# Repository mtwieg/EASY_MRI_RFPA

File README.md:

# EASY_MRI_RFPA
Click the "Wiki" tab above to view the tutorials and other info!

DISCLAIMER:
None of the designs in this repo have been tested or certified to any safety standards (IEC 60601-1, UL-94, etc). 
Intended for non-clinical, research use only.
Circuits may involve hazardous voltages, currents, and temperatures.
For non-expert users, I highly recommend never touching the circuitry while power is being applied. Circuitry may be probed, but probes should not be moved or tampered with while power is applied.

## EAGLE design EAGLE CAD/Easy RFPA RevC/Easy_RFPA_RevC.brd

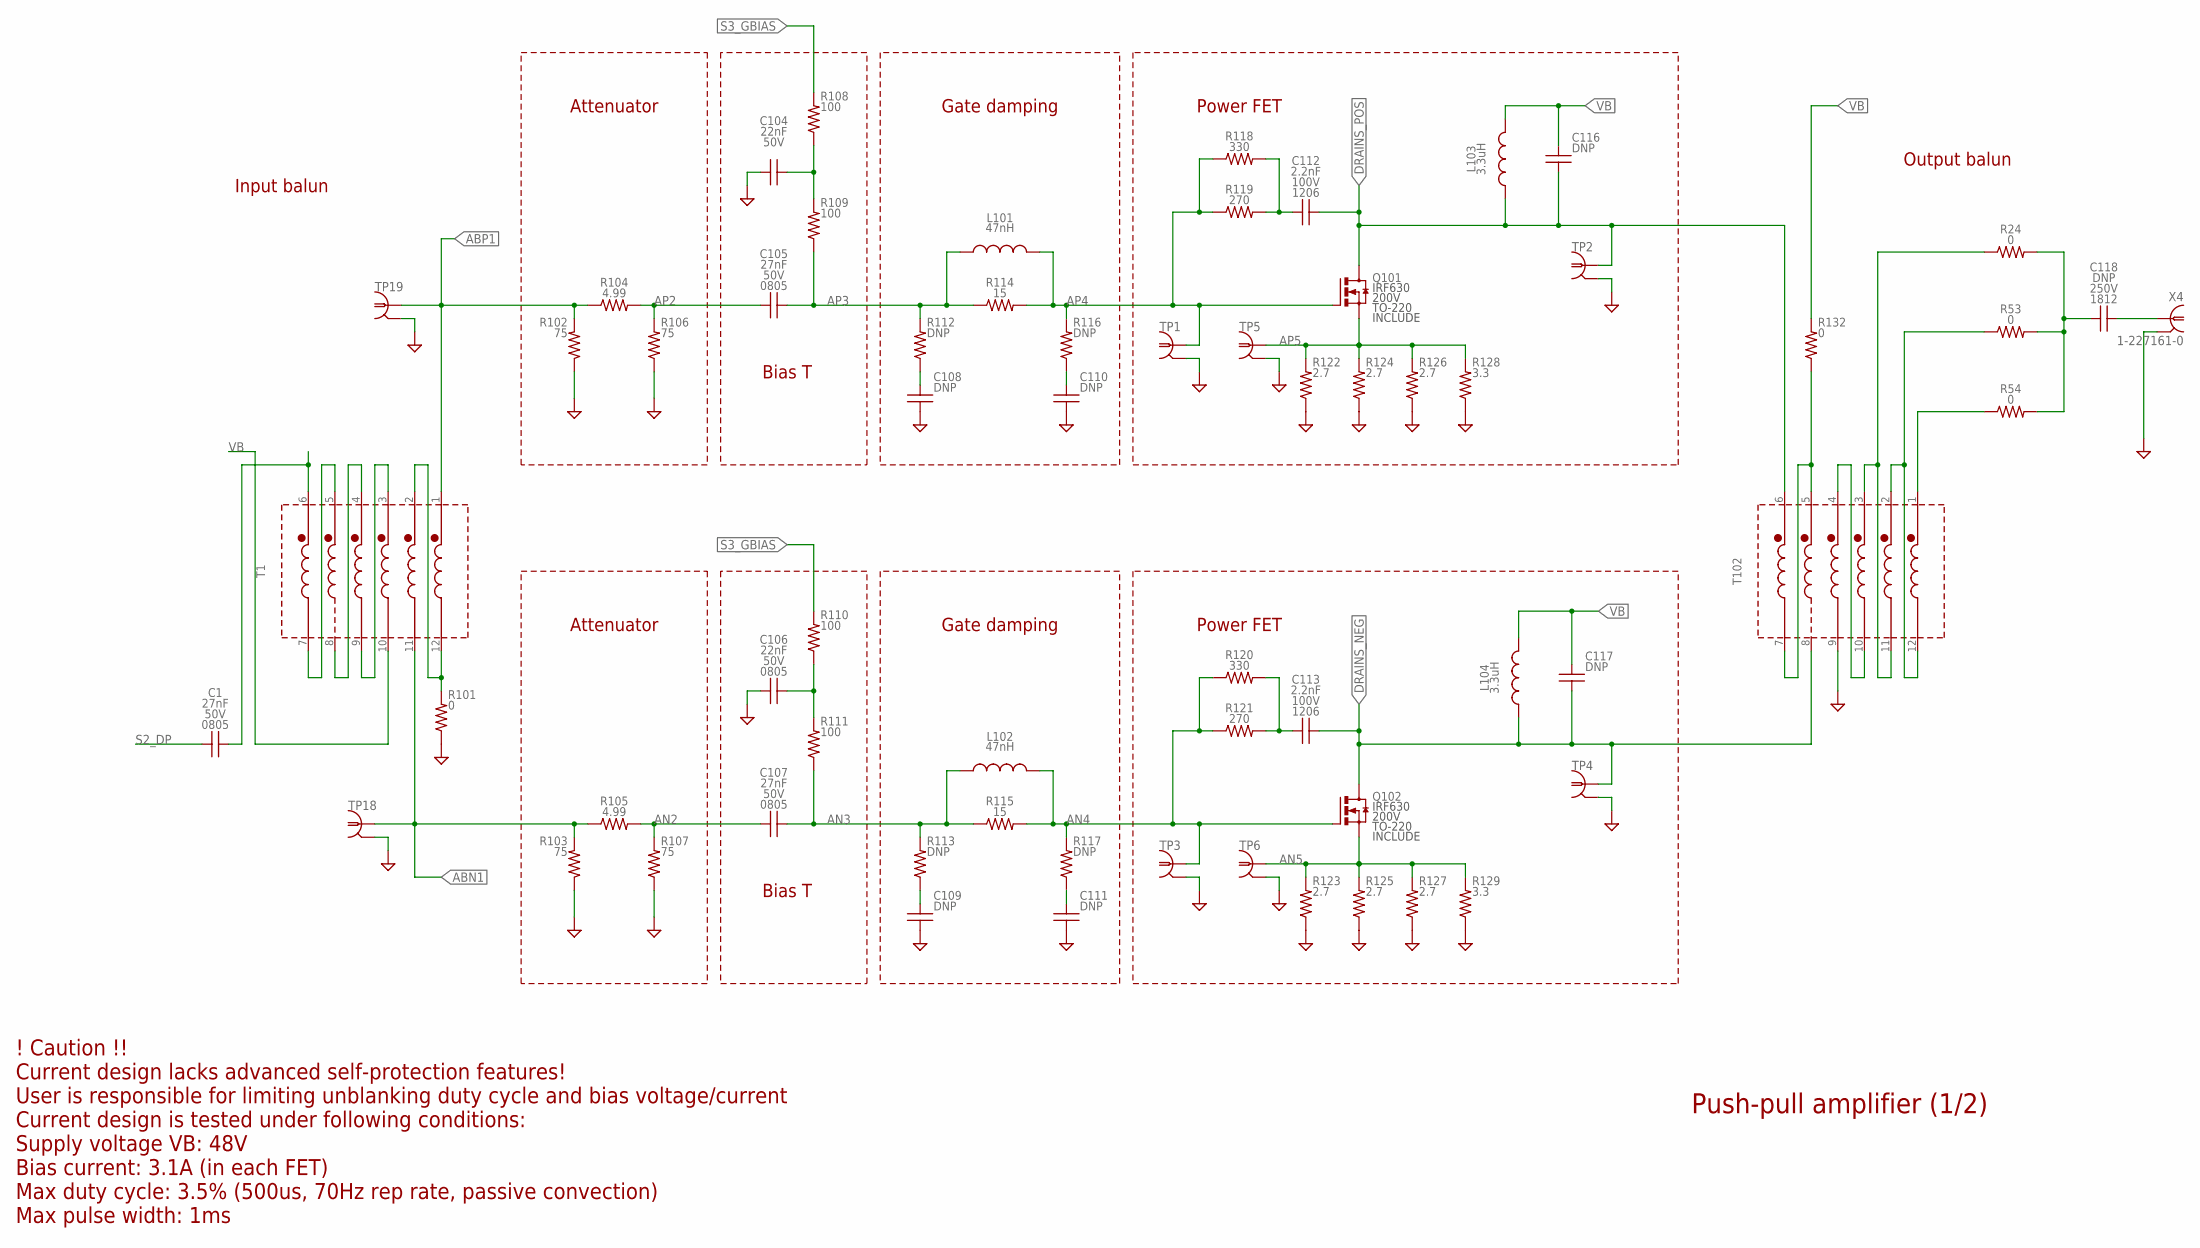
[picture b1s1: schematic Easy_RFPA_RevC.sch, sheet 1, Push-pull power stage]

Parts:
C1, C105, C107: 27nF; 0805_IPC-7351B; VOLTAGE 50V
C104, C106: 22nF; 0805_IPC-7351B; VOLTAGE 50V
C108, C109, C110, C111: DNP; 0805_IPC-7351B; VOLTAGE 50V
C112, C113: 2.2nF; C1206; VOLTAGE 100V
C116, C117: DNP; C1812; VOLTAGE 100V
C118: DNP; C1812; VOLTAGE 250V
L101, L102: 47nH; L1008
L103, L104: 3.3uH; DR127
Q101: IRF520N; TO220BV
Q102: IRF630; TO220BV
R24, R53, R54: 0; 1206_IPC-7351B
R101, R132: 0; 0805_IPC-7351B
R102, R103, R106, R107: 75; 1206_IPC-7351B
R104, R105: 4.99; 1206_IPC-7351B
R108, R110: 100; 0805_IPC-7351B
R109, R111: 100; 1206_IPC-7351B
R112, R113, R116, R117: DNP; 0805_IPC-7351B
R114, R115: 15; 0805_IPC-7351B
R118, R120: 330; R2512
R119, R121: 270; R2512
R122, R123, R124, R125, R126, R127: 2.7; R2512
R128, R129: 3.3; R2512
T1: HP1_TRAFO; HP1
T102: HP4_TRAFO; HP4
TP1, TP3, TP18, TP19: PROBE_TPTP_5MM; PROBE_TP_5MM
TP2, TP4, TP5, TP6: PROBE_TPTP_7P5MM; PROBE_TP_7P5MM
X4: 1-227161-0; AMP_227161

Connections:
ABN1: R103.1, R105.1, T1.11 (F2), TP18.TP (1); also elsewhere on the board
ABP1: R102.1, R104.1, T1.1 (S1), TP19.TP (1); also elsewhere on the board
AN2: C107.2, R105.2, R107.1
AN3: C107.1, L102.1, R111.2, R113.1, R115.1
AN4: L102.2, Q102.G, R115.2, R117.1, R120.1, R121.1, TP3.TP (1)
AN5: Q102.S, R123.1, R125.1, R127.1, R129.1, TP6.TP (1); also elsewhere on the board
AP2: C105.2, R104.2, R106.1
AP3: C105.1, L101.1, R109.2, R112.1, R114.1
AP4: L101.2, Q101.G, R114.2, R116.1, R118.1, R119.1, TP1.TP (1)
AP5: Q101.S, R122.1, R124.1, R126.1, R128.1, TP5.TP (1); also elsewhere on the board
DRAINS_NEG: C113.2, C117.2, L104.1, Q102.D, T102.8 (F5), TP4.TP (1); also elsewhere on the board
DRAINS_POS: C112.2, C116.2, L103.1, Q101.D, T102.6 (S6), TP2.TP (1); also elsewhere on the board
GND: C104.2, C106.2, C108.2, C109.2, C110.2, C111.2, R101.2, R102.2, R103.2, R106.2, R107.2, R122.2, R123.2, R124.2, R125.2, R126.2, R127.2, R128.2, R129.2, T102.9 (F4), TP1.GND (GND1), TP2.GND (GND1), TP3.GND (GND1), TP4.GND (GND1), TP5.GND (GND1), TP6.GND (GND1), TP18.GND (GND1), TP19.GND (GND1), X4.2; also elsewhere on the board
unnamed: C113.1, R120.2, R121.2
unnamed: C109.1, R113.2
unnamed: C104.1, R108.2, R109.1
unnamed: C108.1, R112.2
unnamed: C110.1, R116.2
unnamed: C112.1, R118.2, R119.2
unnamed: C106.1, R110.2, R111.1
unnamed: C111.1, R117.2
unnamed: R53.1, T102.2 (S2), T102.12 (F1)
unnamed: R54.1, T102.1 (S1)
unnamed: C118.2, X4.1
unnamed: C1.1, T1.6 (S6)
unnamed: R24.1, T102.3 (S3), T102.11 (F2)
unnamed: T102.4 (S4), T102.10 (F3)
unnamed: C118.1, R24.2, R53.2, R54.2
S2_DP: C1.2; also elsewhere on the board
S3_GBIAS: R108.1, R110.1; also elsewhere on the board
T1_CT: R101.1, T1.2 (S2), T1.12 (F1)
T1_P1: T1.5 (S5), T1.7 (F6)
T1_P2: T1.4 (S4), T1.8 (F5)
T1_P3: T1.3 (S3), T1.9 (F4)
VB: C116.1, C117.1, L103.2, L104.2, R132.1, T1.10 (F3); also elsewhere on the board
VB_CT: R132.2, T102.5 (S5), T102.7 (F6)

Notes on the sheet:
Attenuator
Bias T
Gate damping
Power FET
Input balun
Output balun
! Caution !! Current design lacks advanced self-protection features! User is responsible for limiting unblanking duty cycle and bias voltage/current Current design is tested under following conditions: Supply voltage VB: 48V Bias current: 3.1A (in each FET) Max duty cycle: 3.5% (500us, 70Hz rep rat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
Push-pull amplifier (1/2)

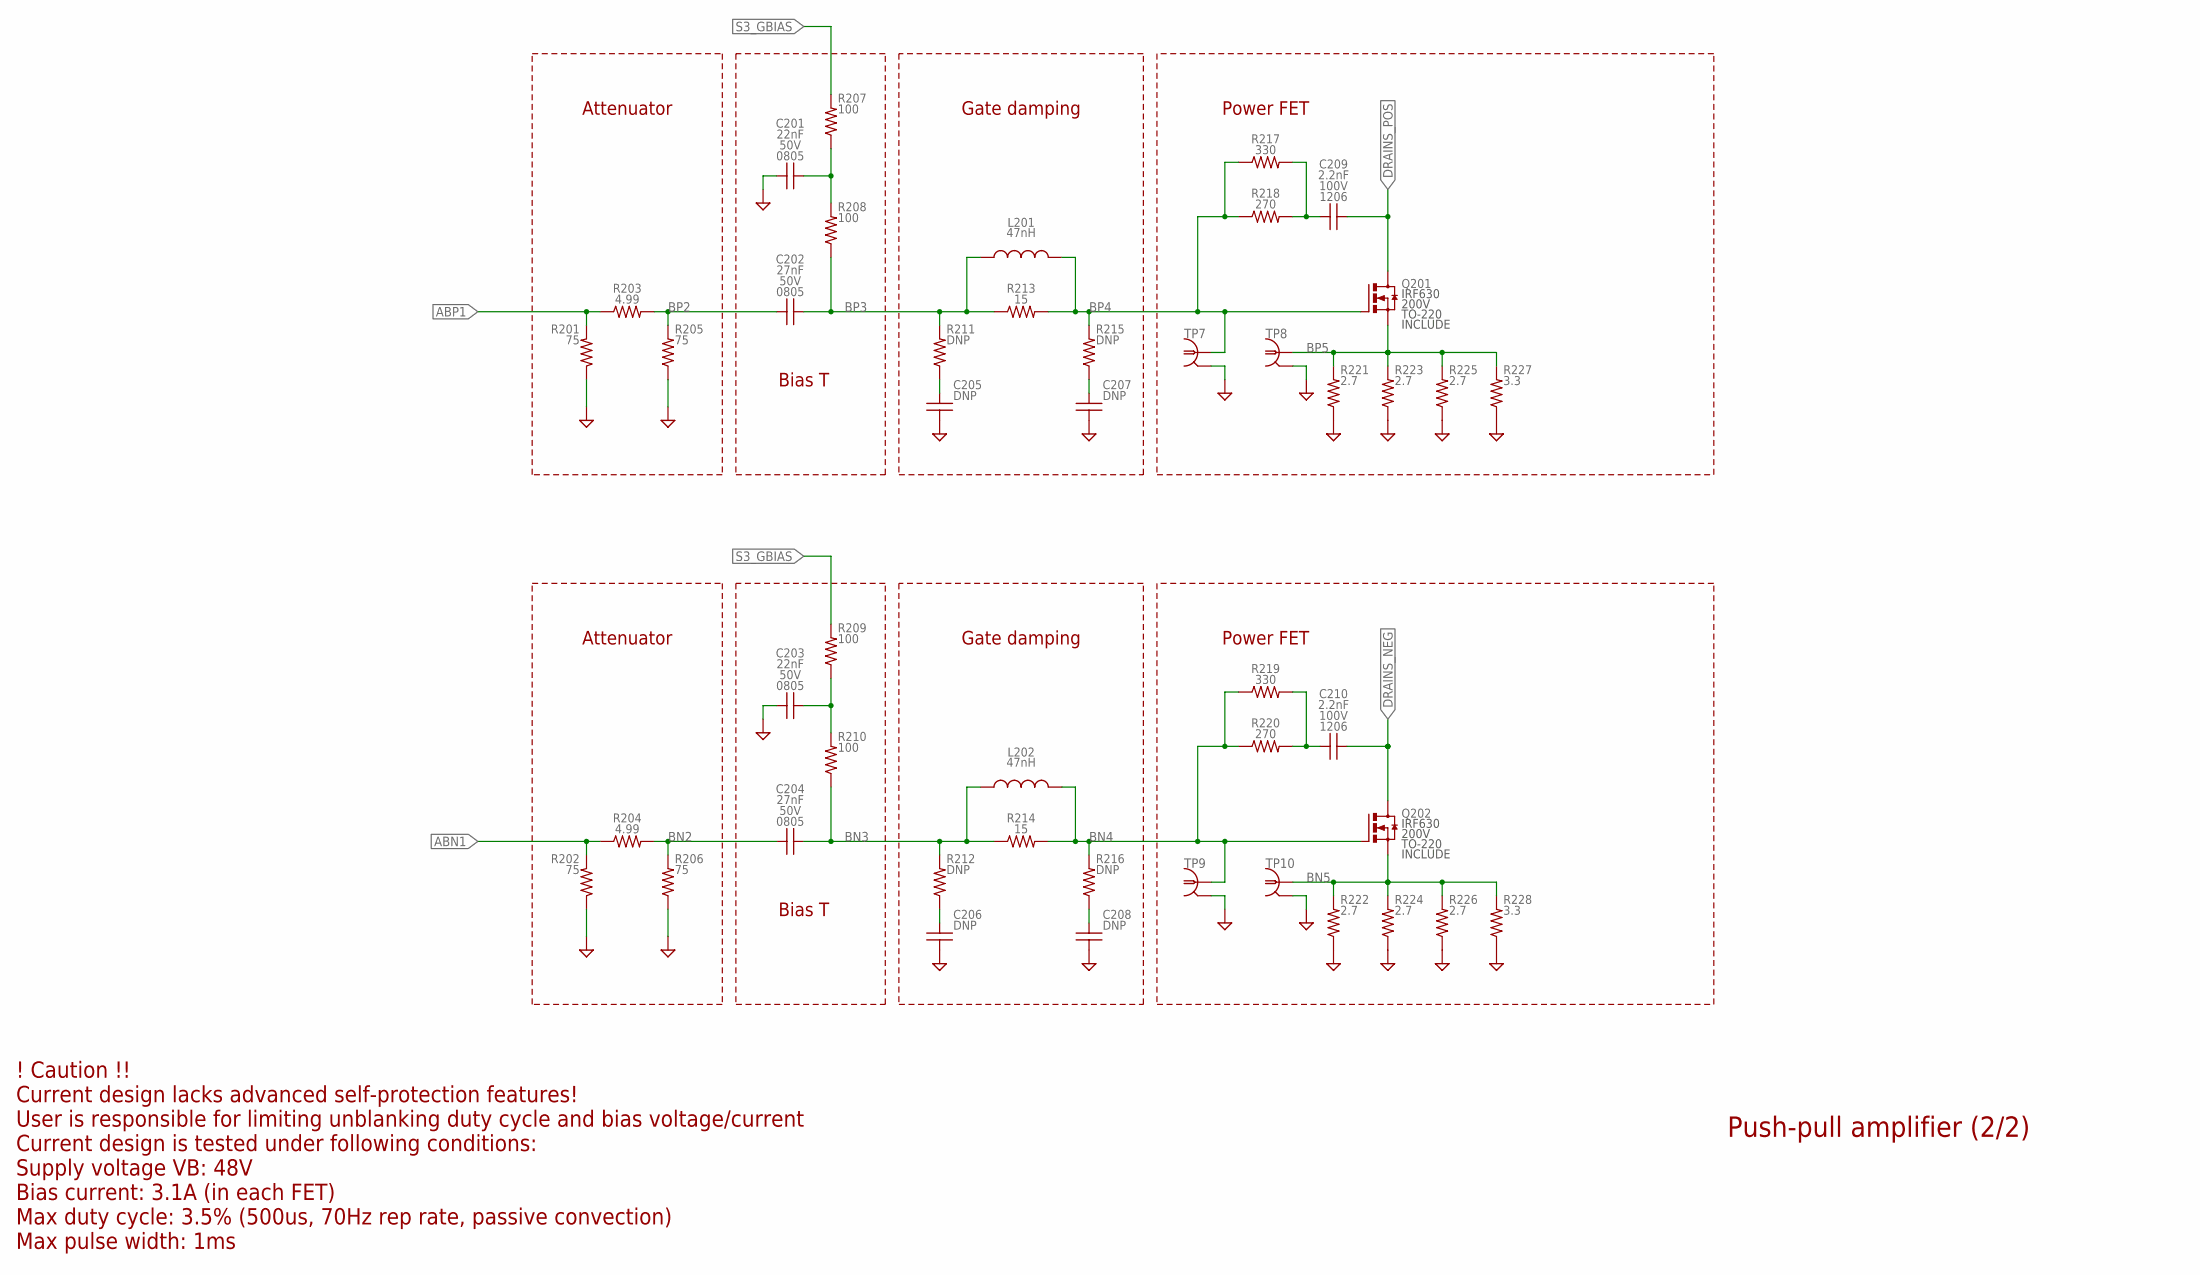
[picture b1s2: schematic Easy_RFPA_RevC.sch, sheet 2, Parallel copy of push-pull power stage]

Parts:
C201, C203: 22nF; 0805_IPC-7351B; VOLTAGE 50V
C202, C204: 27nF; 0805_IPC-7351B; VOLTAGE 50V
C205, C206, C207, C208: DNP; 0805_IPC-7351B; VOLTAGE 50V
C209, C210: 2.2nF; C1206; VOLTAGE 100V
L201, L202: 47nH; L1008
Q201, Q202: IRF630; TO220BV
R201, R202, R205, R206: 75; 1206_IPC-7351B
R203, R204: 4.99; 1206_IPC-7351B
R207, R209: 100; 0805_IPC-7351B
R208, R210: 100; 1206_IPC-7351B
R211, R212, R215, R216: DNP; 0805_IPC-7351B
R213, R214: 15; 0805_IPC-7351B
R217, R219: 330; R2512
R218, R220: 270; R2512
R221, R222, R223, R224, R225, R226: 2.7; R2512
R227, R228: 3.3; R2512
TP7, TP9: PROBE_TPTP_5MM; PROBE_TP_5MM
TP8, TP10: PROBE_TPTP_7P5MM; PROBE_TP_7P5MM

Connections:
ABN1: R202.1, R204.1; also elsewhere on the board
ABP1: R201.1, R203.1; also elsewhere on the board
BN2: C204.2, R204.2, R206.1
BN3: C204.1, L202.1, R210.2, R212.1, R214.1
BN4: L202.2, Q202.G, R214.2, R216.1, R219.1, R220.1, TP9.TP (1)
BN5: Q202.S, R222.1, R224.1, R226.1, R228.1, TP10.TP (1); also elsewhere on the board
BP2: C202.2, R203.2, R205.1
BP3: C202.1, L201.1, R208.2, R211.1, R213.1
BP4: L201.2, Q201.G, R213.2, R215.1, R217.1, R218.1, TP7.TP (1)
BP5: Q201.S, R221.1, R223.1, R225.1, R227.1, TP8.TP (1); also elsewhere on the board
DRAINS_NEG: C210.2, Q202.D; also elsewhere on the board
DRAINS_POS: C209.2, Q201.D; also elsewhere on the board
GND: C201.2, C203.2, C205.2, C206.2, C207.2, C208.2, R201.2, R202.2, R205.2, R206.2, R221.2, R222.2, R223.2, R224.2, R225.2, R226.2, R227.2, R228.2, TP7.GND (GND1), TP8.GND (GND1), TP9.GND (GND1), TP10.GND (GND1); also elsewhere on the board
unnamed: C203.1, R209.2, R210.1
unnamed: C206.1, R212.2
unnamed: C208.1, R216.2
unnamed: C210.1, R219.2, R220.2
unnamed: C201.1, R207.2, R208.1
unnamed: C205.1, R211.2
unnamed: C207.1, R215.2
unnamed: C209.1, R217.2, R218.2
S3_GBIAS: R207.1, R209.1; also elsewhere on the board

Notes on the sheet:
Attenuator
Bias T
Gate damping
Power FET
! Caution !! Current design lacks advanced self-protection features! User is responsible for limiting unblanking duty cycle and bias voltage/current Current design is tested under following conditions: Supply voltage VB: 48V Bias current: 3.1A (in each FET) Max duty cycle: 3.5% (500us, 70Hz rep rat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
Push-pull amplifier (2/2)

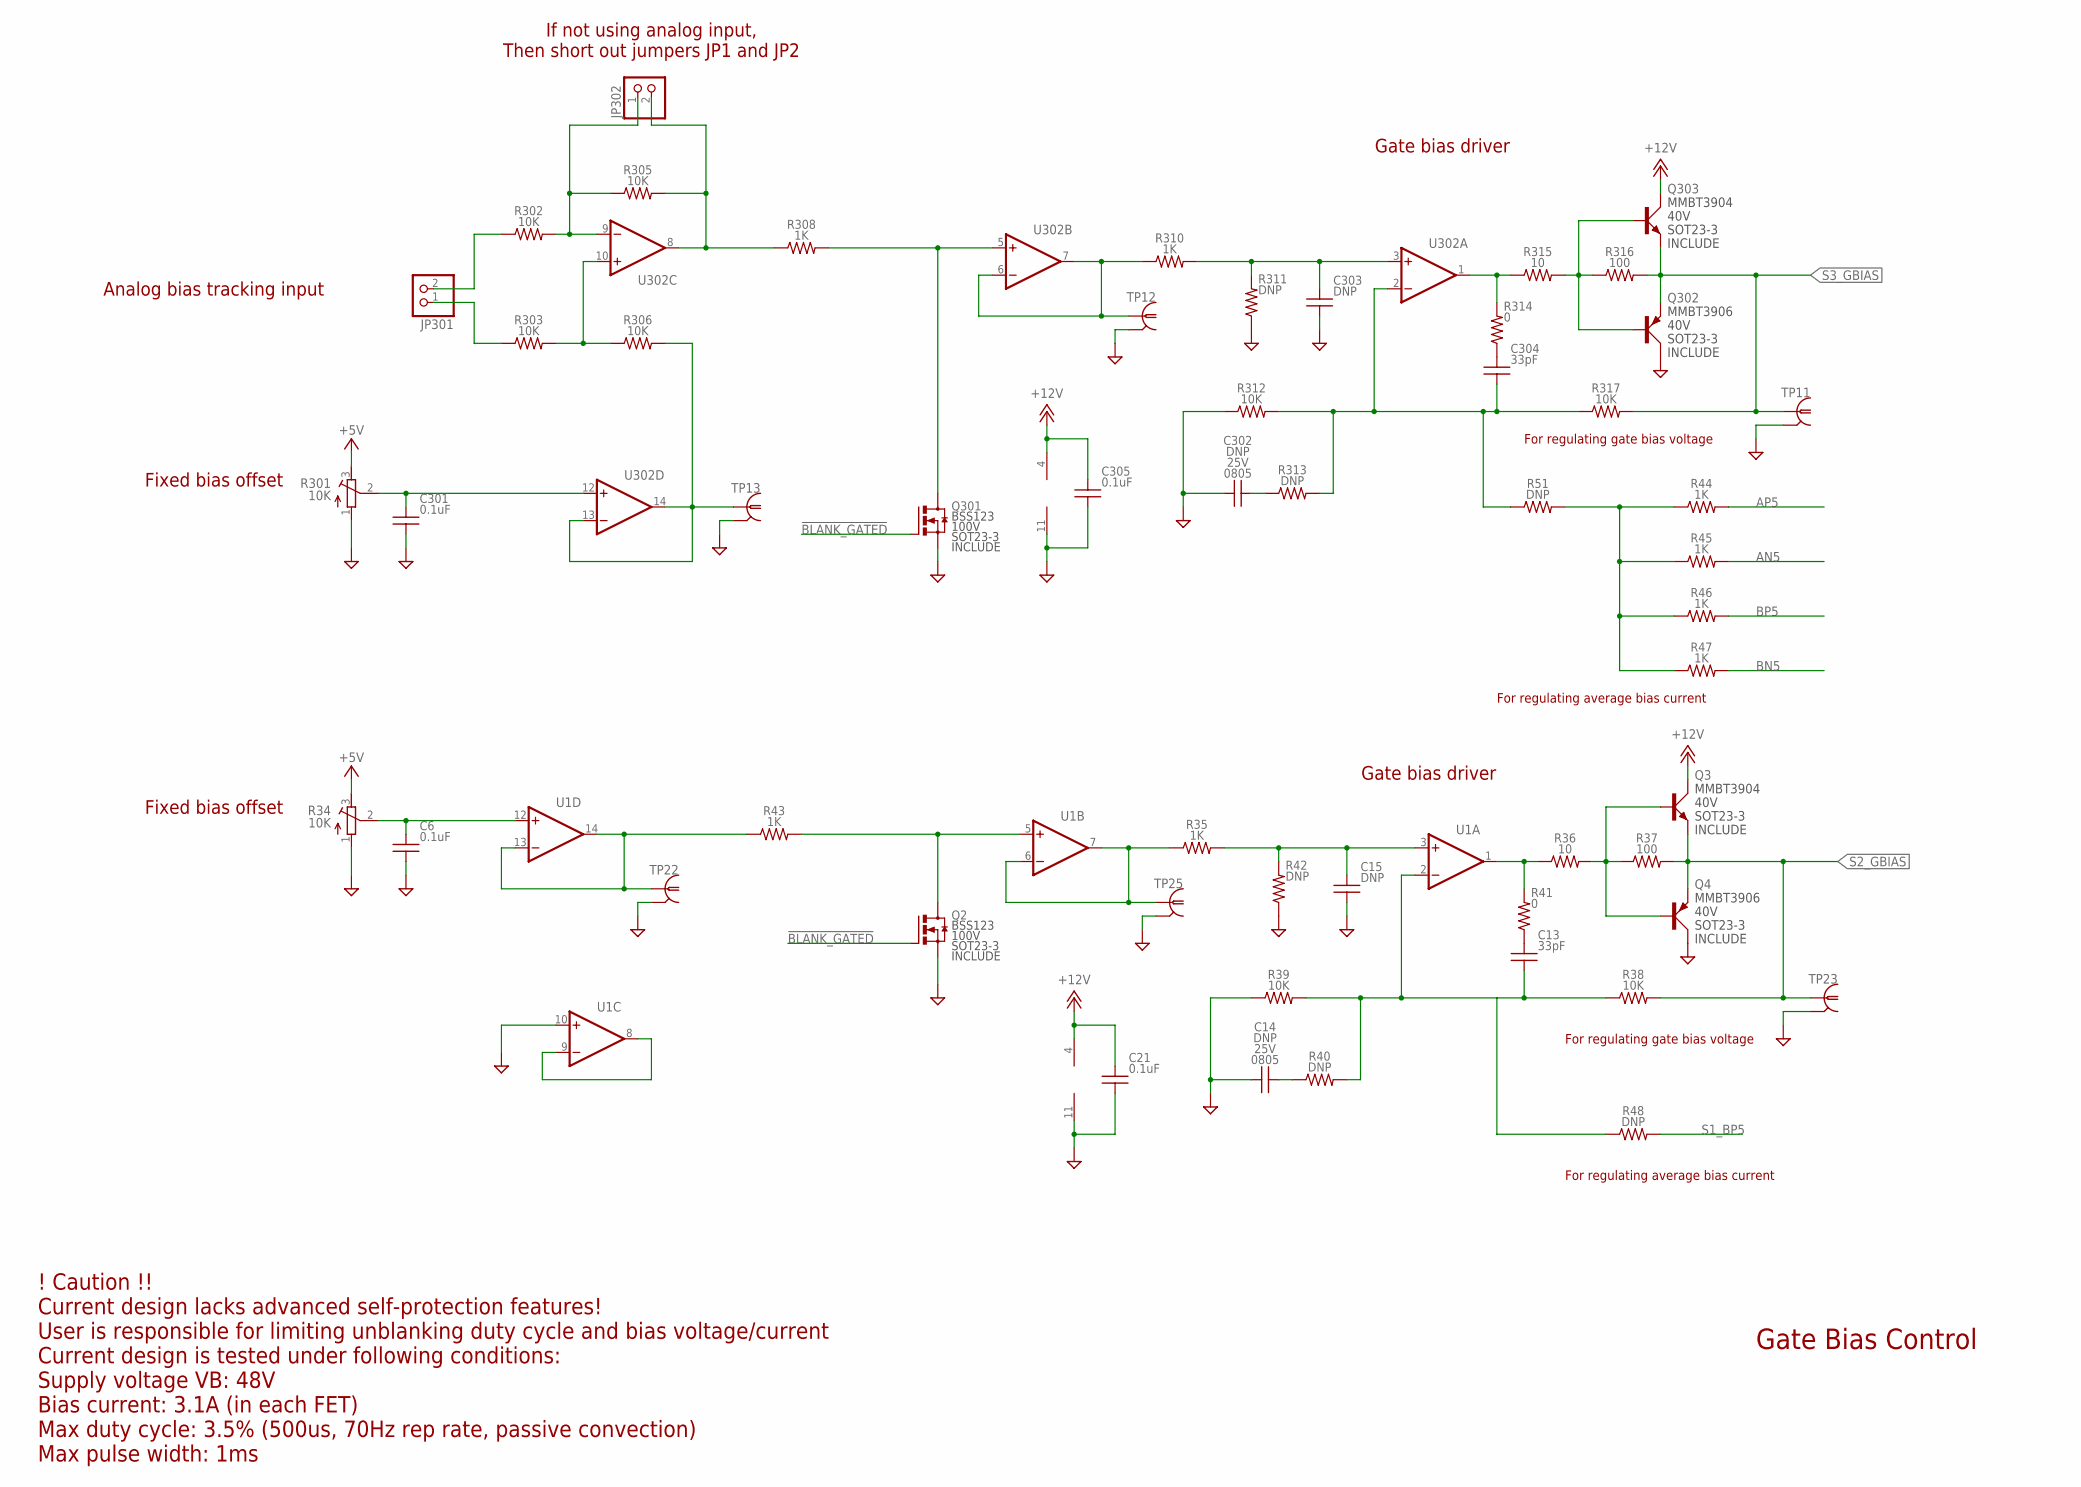
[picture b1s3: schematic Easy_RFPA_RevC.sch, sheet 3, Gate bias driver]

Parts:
C6, C21, C301, C305: 0.1uF; 0805_IPC-7351B; VOLTAGE 25V
C13, C304: 33pF; 0805_IPC-7351B; VOLTAGE 50V
C14, C15, C302, C303: DNP; 0805_IPC-7351B; VOLTAGE 25V
JP301, JP302: PINHD-1X2; 1X02
Q2, Q301: MOSFET_NBSS123SOT23; SOT23R_INFINEON
Q3, Q303: NPNMMBT3904SOT23_BEC; SOT23R_INFINEON
Q4, Q302: PNPSOT23_BEC; SOT23R_INFINEON
R34, R301: 10K; RTRIM3299W
R35, R43, R44, R45, R46, R47, R308, R310: 1K; 0805_IPC-7351B
R36, R315: 10; 0805_IPC-7351B
R37, R316: 100; 0805_IPC-7351B
R38, R39, R302, R303, R305, R306, R312, R317: 10K; 0805_IPC-7351B
R40, R42, R48, R51, R311, R313: DNP; 0805_IPC-7351B
R41, R314: 0; 0805_IPC-7351B
TP11, TP12, TP13, TP22, TP23, TP25: PROBE_TPTP_5MM; PROBE_TP_5MM
U1, U302: OPAMP_QUADTLV274IDSOIC14; SO14

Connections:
!BLANK_GATED: Q2.1 (G), Q301.1 (G); also elsewhere on the board
+5V: R34.3 (E), R301.3 (E); also elsewhere on the board
+12V: C21.1, C305.1, Q3.3 (C), Q303.3 (C), U1.4 (V+), U302.4 (V+); also elsewhere on the board
AN5: R45.2; also elsewhere on the board
AP5: R44.2; also elsewhere on the board
BN5: R47.2; also elsewhere on the board
BP5: R46.2; also elsewhere on the board
GND: C6.2, C14.2, C15.2, C21.2, C301.2, C302.2, C303.2, C305.2, Q2.2 (S), Q4.3 (C), Q301.2 (S), Q302.3 (C), R34.1 (A), R39.1, R42.2, R301.1 (A), R311.2, R312.1, TP11.GND (GND1), TP12.GND (GND1), TP13.GND (GND1), TP22.GND (GND1), TP23.GND (GND1), TP25.GND (GND1), U1.10 (+IN), U1.11 (V-), U302.11 (V-); also elsewhere on the board
unnamed: R314.1, R315.1, U302.1 (OUT)
unnamed: Q302.1 (B), Q303.1 (B), R315.2, R316.1
unnamed: R310.1, TP12.TP (1), U302.6 (-IN), U302.7 (OUT)
unnamed: C304.1, R314.2
unnamed: C302.1, R313.1
unnamed: C304.2, R51.1, R312.2, R313.2, R317.1, U302.2 (-IN)
unnamed: C303.1, R310.2, R311.1, U302.3 (+IN)
unnamed: R303.2, R306.1, U302.10 (+IN)
unnamed: JP302.2, R305.2, R308.1, U302.8 (OUT)
unnamed: JP302.1, R302.2, R305.1, U302.9 (-IN)
unnamed: JP301.2, R302.1
unnamed: JP301.1, R303.1
unnamed: R44.1, R45.1, R46.1, R47.1, R51.2
unnamed: Q301.3 (D), R308.2, U302.5 (+IN)
unnamed: R43.1, TP22.TP (1), U1.13 (-IN), U1.14 (OUT)
unnamed: C301.1, R301.2 (S), U302.12 (+IN)
unnamed: R306.2, TP13.TP (1), U302.13 (-IN), U302.14 (OUT)
unnamed: C6.1, R34.2 (S), U1.12 (+IN)
unnamed: R36.1, R41.1, U1.1 (OUT)
unnamed: U1.8 (OUT), U1.9 (-IN)
unnamed: Q3.1 (B), Q4.1 (B), R36.2, R37.1
unnamed: C13.2, R38.1, R39.2, R40.2, R48.1, U1.2 (-IN)
unnamed: C15.1, R35.2, R42.1, U1.3 (+IN)
unnamed: C14.1, R40.1
unnamed: R35.1, TP25.TP (1), U1.6 (-IN), U1.7 (OUT)
unnamed: C13.1, R41.2
unnamed: Q2.3 (D), R43.2, U1.5 (+IN)
S1_BP5: R48.2; also elsewhere on the board
S2_GBIAS: Q3.2 (E), Q4.2 (E), R37.2, R38.2, TP23.TP (1); also elsewhere on the board
S3_GBIAS: Q302.2 (E), Q303.2 (E), R316.2, R317.2, TP11.TP (1); also elsewhere on the board

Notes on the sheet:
If not using analog input, Then short out jumpers JP1 and JP2
Analog bias tracking input
Fixed bias offset
Gate bias driver
! Caution !! Current design lacks advanced self-protection features! User is responsible for limiting unblanking duty cycle and bias voltage/current Current design is tested under following conditions: Supply voltage VB: 48V Bias current: 3.1A (in each FET) Max duty cycle: 3.5% (500us, 70Hz rep rat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
Gate Bias Control
For regulating average bias current
For regulating gate bias voltage

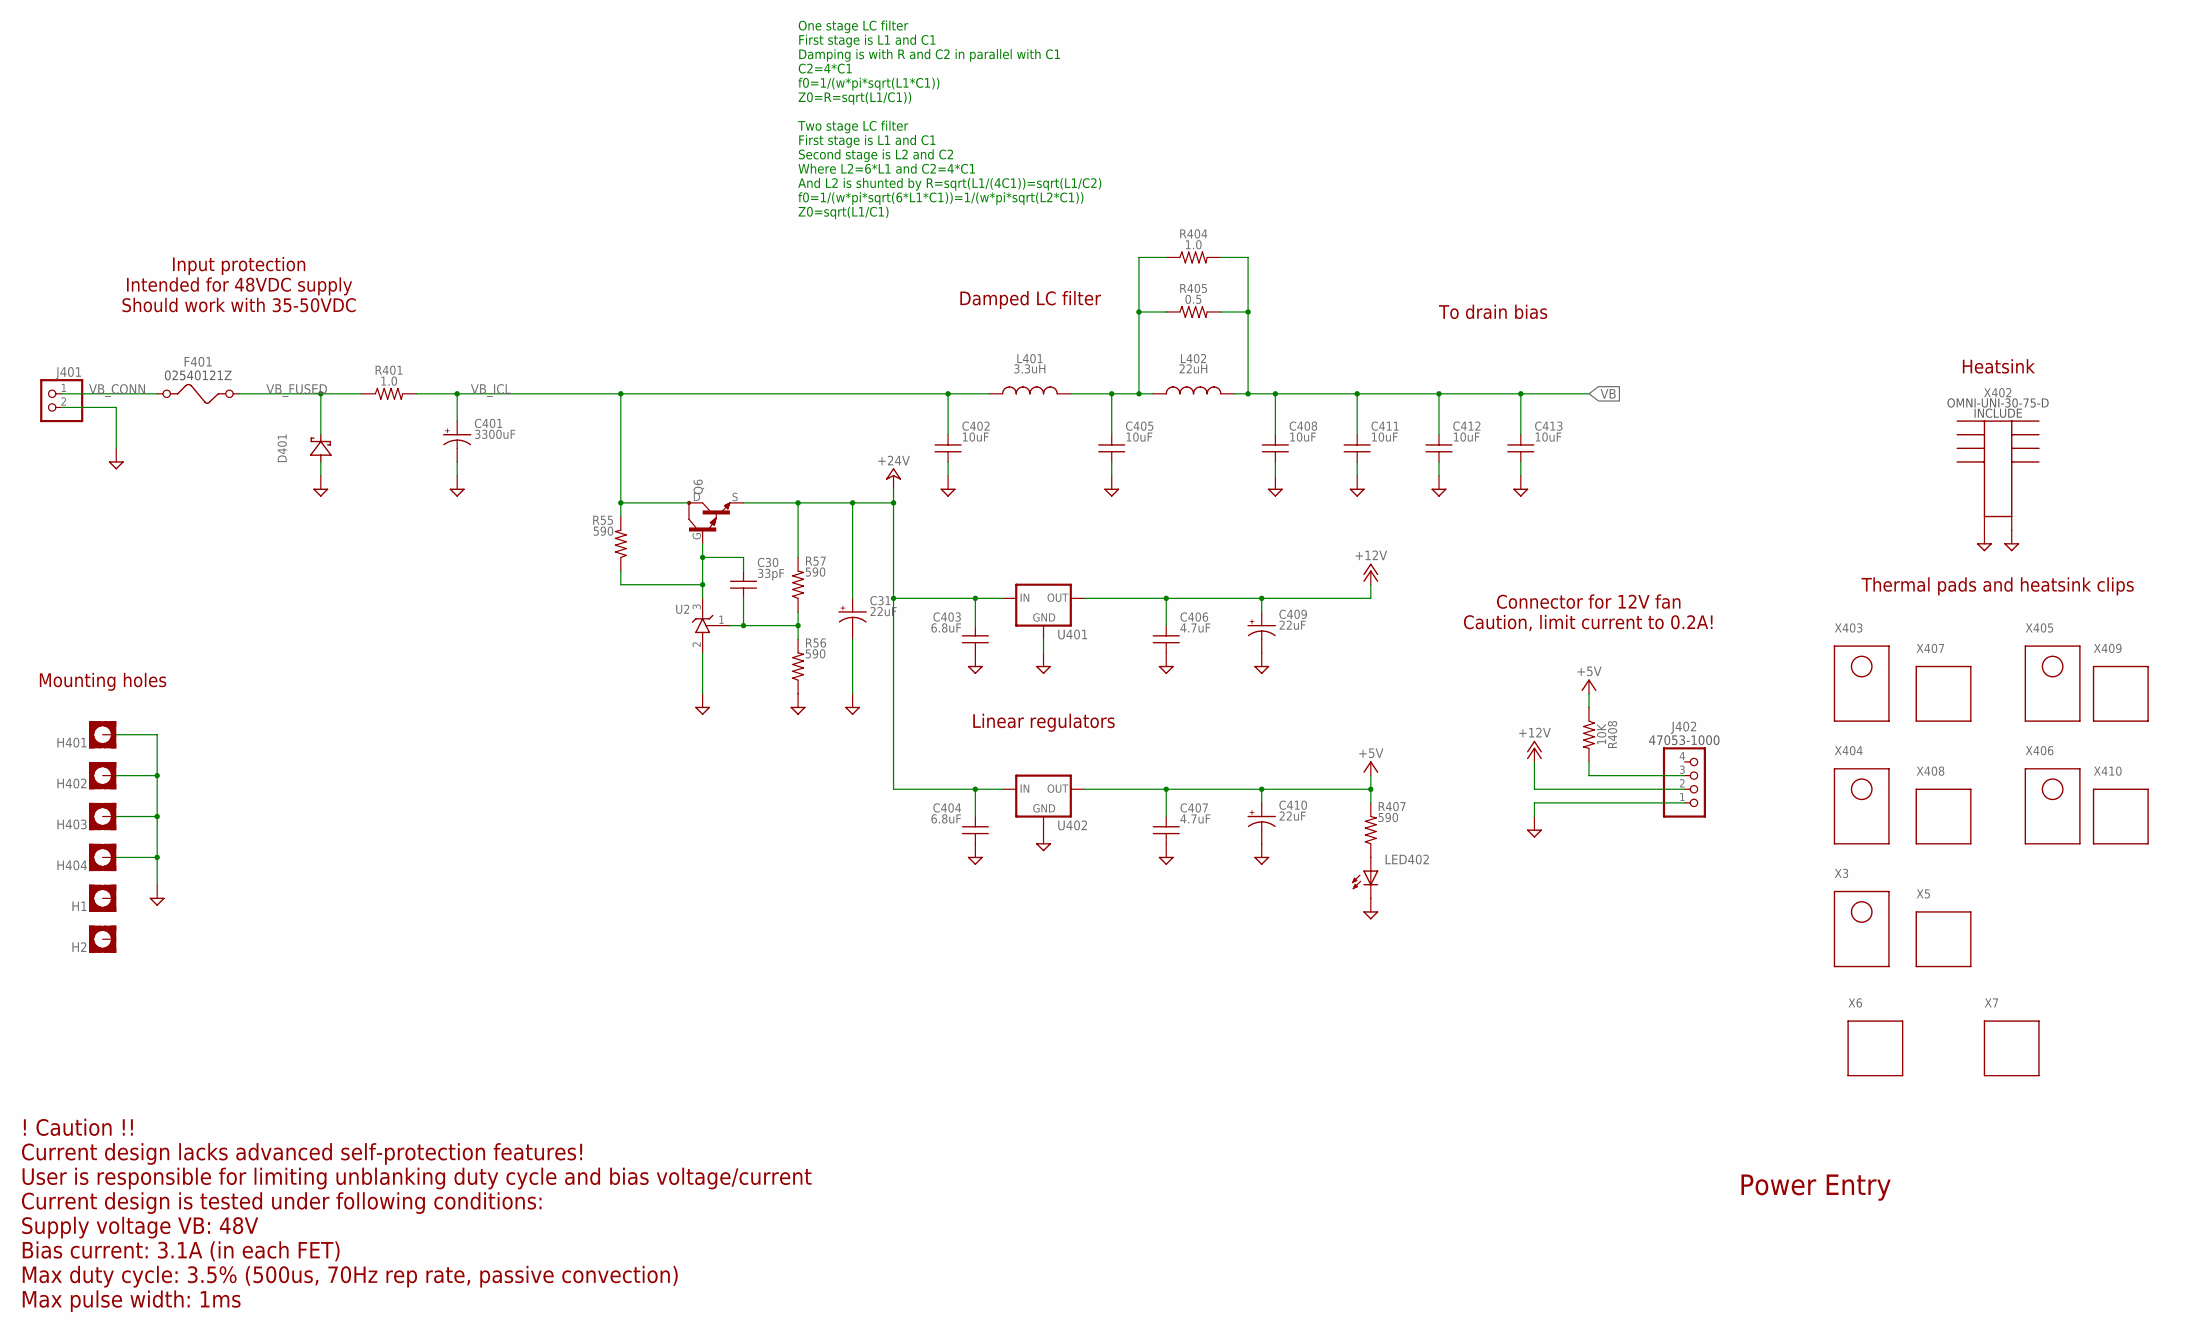
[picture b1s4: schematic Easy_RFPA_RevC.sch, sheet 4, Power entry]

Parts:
C30: 33pF; 0805_IPC-7351B; VOLTAGE 50V
C31, C409, C410: 22uF; E2,5-7
C401: 3300uF; EB25D
C402, C405, C408, C411, C412, C413: 10uF; C2220_CKG57N
C403, C404: 6.8uF; C1210; VOLTAGE 50V
C406, C407: 4.7uF; C1206; VOLTAGE 50V
D401: D-SCHOTTKYSK810L-TPSMC; DO-214AB(SMC)
F401: FUSE_2P; 02540121Z
H1, H2, H401, H402, H403, H404: MOUNT-PAD-SQUARE3.2; 3,2-PAD-SQUARE
J401: HDR_2X1282836-1282836-1; W237-02
J402: KK_PCFAN; 47053-1000
L401: 3.3uH; DR127
L402: 22uH; DR127
LED402: LEDT1_3/4_RA; LED_5MM_RA
Q6: NPN_DARGLINGTONTIP122TO220BV; TO220BV
R55, R56, R57, R407: 590; 0805_IPC-7351B
R401: 1.0; P0817V
R404: 1.0; 1206_IPC-7351B
R405: 0.5; 1206_IPC-7351B
R408: 10K; 0805_IPC-7351B
U2: ADJ_ZENERTL431AILPRAGTO-92-LPRE; TO-92-FORMED
U401: LDO_3TERMMC78M12CTGTO220_VERT; TO220BV
U402: LDO_3TERMMC78M05CTGTO220_VERT; TO220BV
X6, X7: HEATSINK_CLIPONATS-PCBT1085ATS-PCBT1085; ATS-PCBT1085
X402: HEATSINK_OMNI_DUALOMNI-UNI-30-75-D30-75-D; OMNI-UNI-30-75-D

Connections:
+5V: C407.1, C410.+, R407.1, R408.1, U402.3 (OUT); also elsewhere on the board
+12V: C406.1, C409.+, J402.2, U401.3 (OUT); also elsewhere on the board
+24V: C31.+, C403.1, C404.1, Q6.S (E), R57.1, U401.1 (IN), U402.1 (IN); also elsewhere on the board
GND: C31.-, C401.-, C402.2, C403.2, C404.2, C405.2, C406.2, C407.2, C408.2, C409.-, C410.-, C411.2, C412.2, C413.2, D401.A (A1), H401.B3,2, H402.B3,2, H403.B3,2, H404.B3,2, J401.2, J402.1, LED402.K (C), R56.2, U2.2 (A), U401.2 (GND), U402.2 (GND), X402.P1, X402.P2; also elsewhere on the board
unnamed: LED402.A, R407.2
unnamed: C405.1, L401.2, L402.1, R404.1, R405.1
unnamed: J402.3, R408.2
unnamed: C30.2, R56.1, R57.2, U2.1 (R)
unnamed: C30.1, Q6.G (B), R55.2, U2.3 (C)
VB: C408.1, C411.1, C412.1, C413.1, L402.2, R404.2, R405.2; also elsewhere on the board
VB_CONN: F401.1, J401.1
VB_FUSED: D401.K (C1), F401.2, R401.1
VB_ICL: C401.+, C402.1, L401.1, Q6.D (C), R55.1, R401.2

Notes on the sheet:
Mounting holes
Heatsink
Input protection Intended for 48VDC supply Should work with 35-50VDC
Damped LC filter
To drain bias
Linear regulators
Connector for 12V fan Caution, limit current to 0.2A!
! Caution !! Current design lacks advanced self-protection features! User is responsible for limiting unblanking duty cycle and bias voltage/current Current design is tested under following conditions: Supply voltage VB: 48V Bias current: 3.1A (in each FET) Max duty cycle: 3.5% (500us, 70Hz rep rat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
Thermal pads and heatsink clips
Power Entry
One stage LC filter First stage is L1 and C1 Damping is with R and C2 in parallel with C1 C2=4*C1 f0=1/(w*pi*sqrt(L1*C1)) Z0=R=sqrt(L1/C1)) Two stage LC filter First stage is L1 and C1 Second stage is L2 and C2 Where L2=6*L1 and C2=4*C1 And L2 is shunted by R=sqrt(L1/(4C1))=sqrt(L1/C2) f0=1/(w*pi*s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

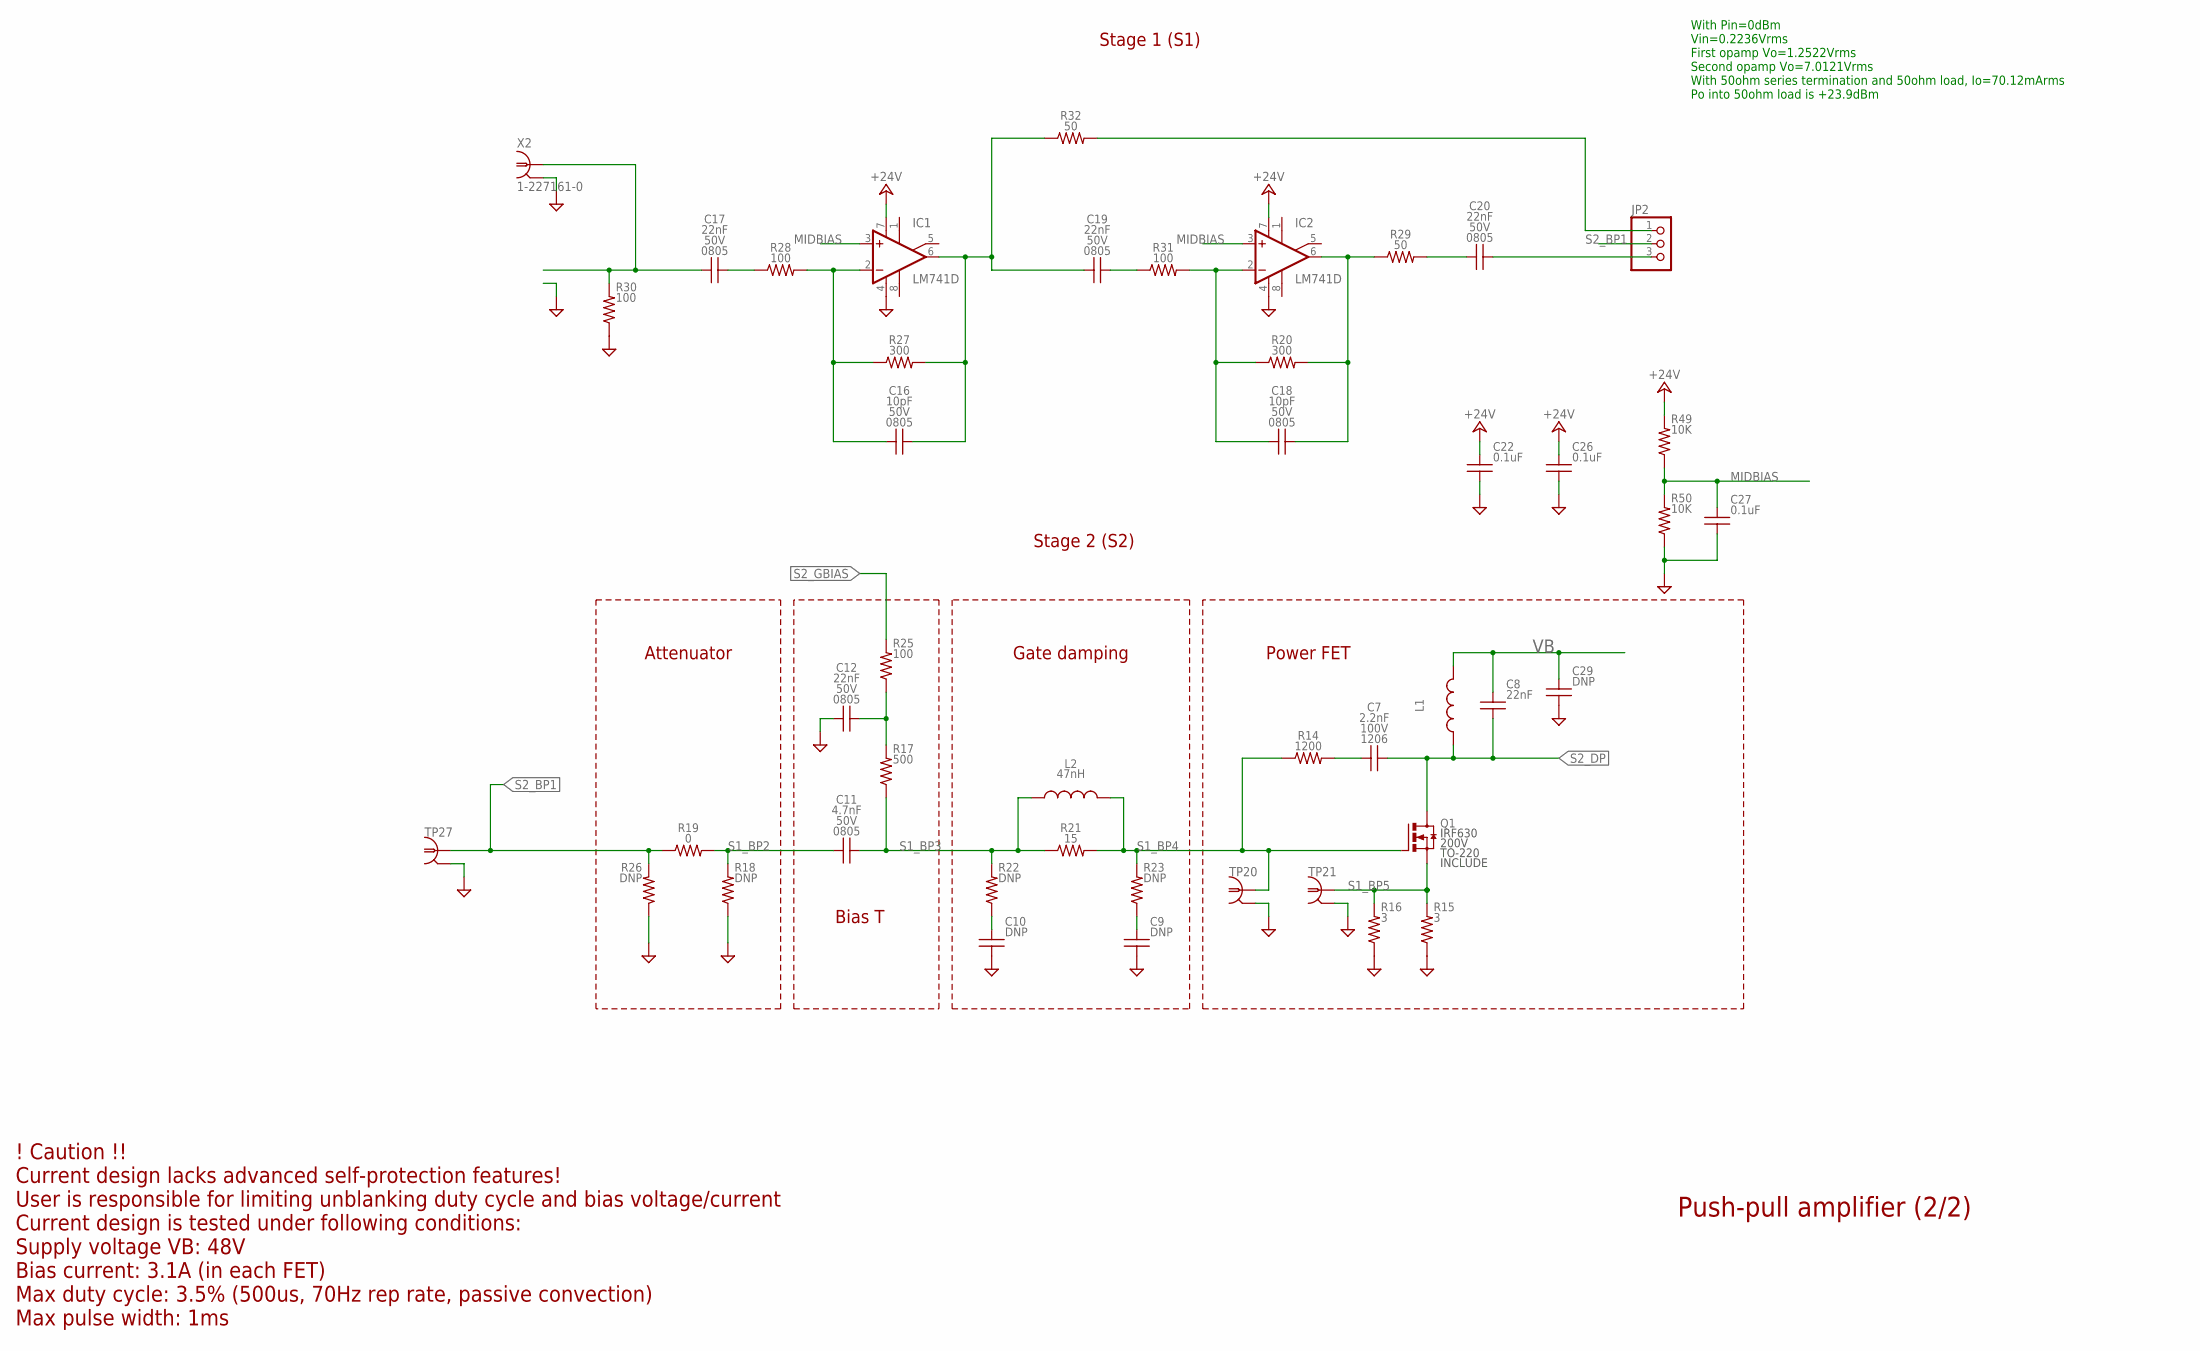
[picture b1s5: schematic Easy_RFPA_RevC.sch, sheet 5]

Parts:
C7: 2.2nF; C1206; VOLTAGE 100V
C8: 22nF; C1206
C9, C10: DNP; 0805_IPC-7351B; VOLTAGE 50V
C11: 4.7nF; 0805_IPC-7351B; VOLTAGE 50V
C12, C17, C19, C20: 22nF; 0805_IPC-7351B; VOLTAGE 50V
C16, C18: 10pF; 0805_IPC-7351B; VOLTAGE 50V
C22, C26, C27: 0.1uF; 0805_IPC-7351B; VOLTAGE 25V
C29: DNP; C1812; VOLTAGE 100V
IC1, IC2: LM741D; SO08
JP2: PINHD-1X3; 1X03
L1: LDR74; DR74
L2: 47nH; L1008
Q1: IRF630; TO220BV
R14: 1200; R2512
R15, R16: 3; R2512
R17: 500; 1206_IPC-7351B
R18, R26: DNP; 1206_IPC-7351B
R19: 0; 1206_IPC-7351B
R20, R27: 300; 0805_IPC-7351B
R21: 15; 0805_IPC-7351B
R22, R23: DNP; 0805_IPC-7351B
R25, R28, R30, R31: 100; 0805_IPC-7351B
R29, R32: 50; 0805_IPC-7351B
R49, R50: 10K; 0805_IPC-7351B
TP20, TP27: PROBE_TPTP_5MM; PROBE_TP_5MM
TP21: PROBE_TPTP_7P5MM; PROBE_TP_7P5MM
X2: 1-227161-0; AMP_227161

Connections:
+24V: C22.1, C26.1, IC1.7 (V+), IC2.7 (V+), R49.1; also elsewhere on the board
GND: C9.2, C10.2, C12.2, C22.2, C26.2, C27.2, C29.2, IC1.4 (V-), IC2.4 (V-), R15.2, R16.2, R18.2, R26.2, R30.2, R50.2, TP20.GND (GND1), TP21.GND (GND1), TP27.GND (GND1), X2.2; also elsewhere on the board
MIDBIAS: C27.1, IC1.3 (+IN), IC2.3 (+IN), R49.2, R50.1
unnamed: C16.2, IC1.2 (-IN), R27.1, R28.2
unnamed: C20.2, R29.2
unnamed: C17.1, R28.1
unnamed: C12.1, R17.1, R25.2
unnamed: C10.1, R22.2
unnamed: C9.1, R23.2
unnamed: C7.1, R14.2
unnamed: C17.2, R30.1, X2.1
unnamed: C19.1, R31.1
unnamed: C18.1, IC2.6 (OUT), R20.2, R29.1
unnamed: C18.2, IC2.2 (-IN), R20.1, R31.2
unnamed: C16.1, C19.2, IC1.6 (OUT), R27.2, R32.1
unnamed: C20.1, JP2.3
unnamed: JP2.1, R32.2
S1_BP2: C11.2, R18.1, R19.2
S1_BP3: C11.1, L2.1, R17.2, R21.1, R22.1
S1_BP4: L2.2, Q1.G, R14.1, R21.2, R23.1, TP20.TP (1)
S1_BP5: Q1.S, R15.1, R16.1, TP21.TP (1); also elsewhere on the board
S2_BP1: JP2.2, R19.1, R26.1, TP27.TP (1)
S2_DP: C7.2, C8.2, L1.1, Q1.D; also elsewhere on the board
S2_GBIAS: R25.1; also elsewhere on the board
VB: C8.1, C29.1, L1.2; also elsewhere on the board

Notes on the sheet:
Attenuator
Bias T
Gate damping
Power FET
! Caution !! Current design lacks advanced self-protection features! User is responsible for limiting unblanking duty cycle and bias voltage/current Current design is tested under following conditions: Supply voltage VB: 48V Bias current: 3.1A (in each FET) Max duty cycle: 3.5% (500us, 70Hz rep rat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
Push-pull amplifier (2/2)
With Pin=0dBm Vin=0.2236Vrms First opamp Vo=1.2522Vrms Second opamp Vo=7.0121Vrms With 50ohm series termination and 50ohm load, Io=70.12mArms Po into 50ohm load is +23.9dBm
Stage 1 (S1)
Stage 2 (S2)

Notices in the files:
parts and their libraries:
dicons: Copyright Field
Set copyright by text with global attribute >COMPANY
